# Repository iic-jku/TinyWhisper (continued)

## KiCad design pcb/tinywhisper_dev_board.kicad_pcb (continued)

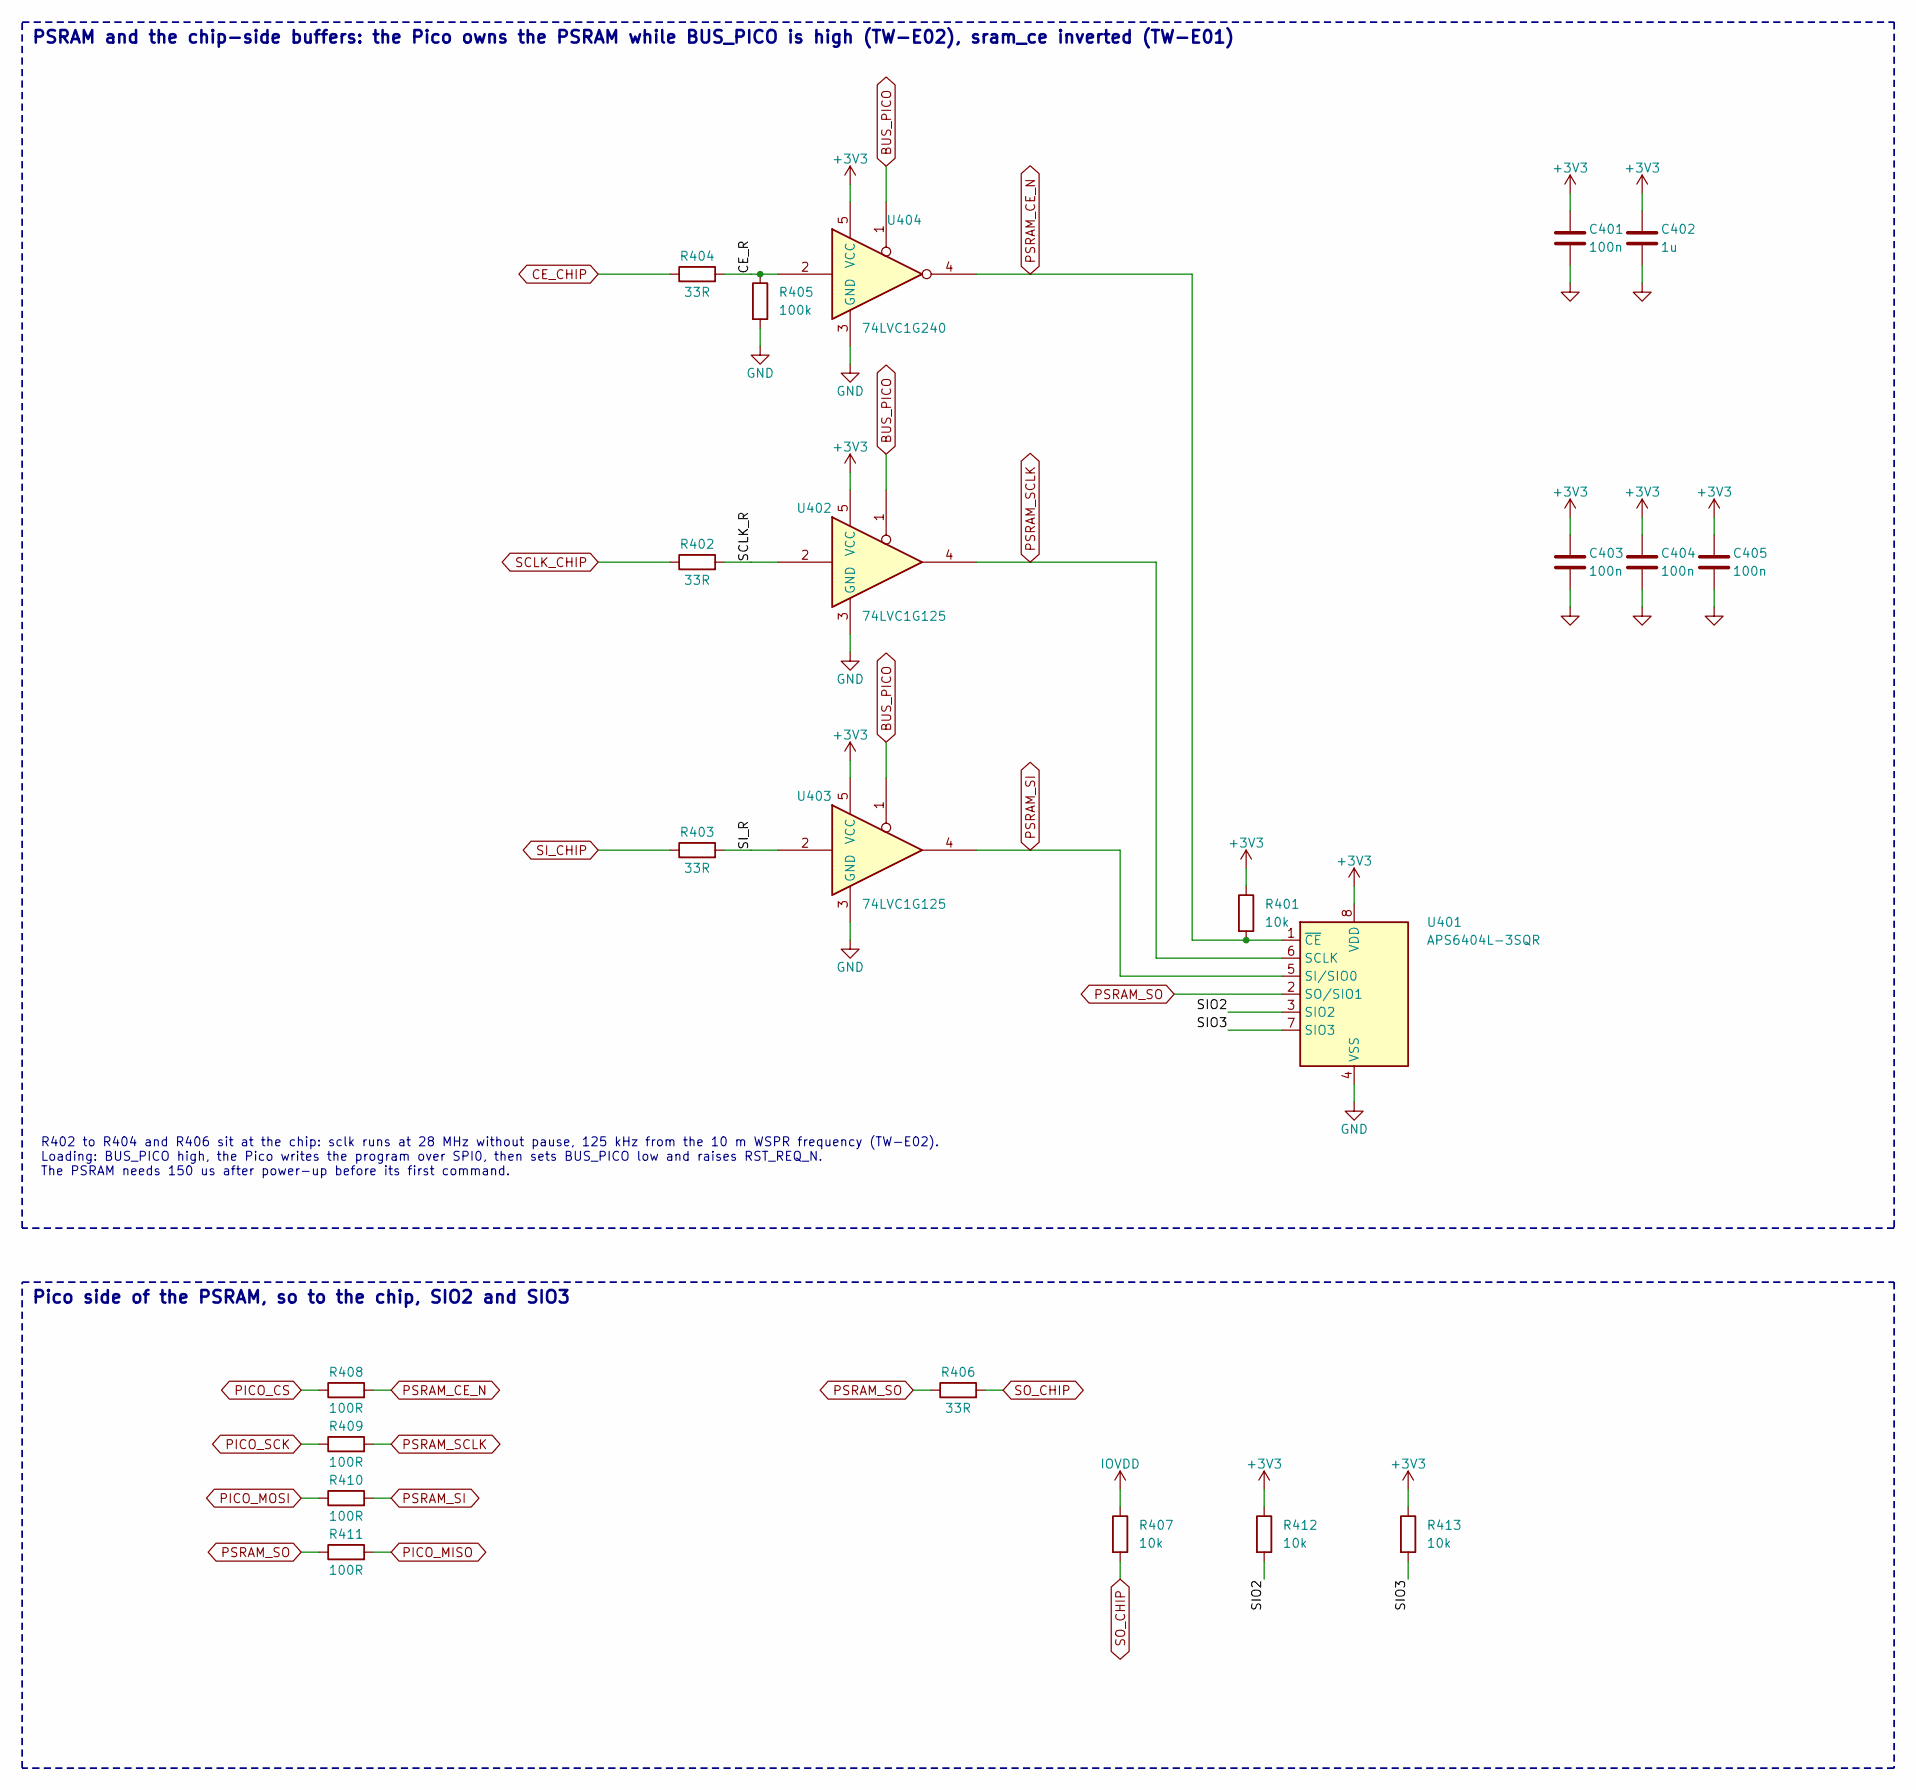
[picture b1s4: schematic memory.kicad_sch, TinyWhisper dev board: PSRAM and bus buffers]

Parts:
C401, C403, C404, C405: 100n; C_0603_1608Metric_Pad1.08x0.95mm_HandSolder; MPN CL10B104KB8NNNC
C402: 1u; C_0603_1608Metric_Pad1.08x0.95mm_HandSolder; MPN CL10B105KO8NNNC
R401, R407, R412, R413: 10k; R_0603_1608Metric_Pad0.98x0.95mm_HandSolder; MPN RC0603FR-0710KL
R402, R403, R404, R406: 33R; R_0603_1608Metric_Pad0.98x0.95mm_HandSolder; MPN RC0603FR-0733RL
R405: 100k; R_0603_1608Metric_Pad0.98x0.95mm_HandSolder; MPN RC0603FR-07100KL
R408, R409, R410, R411: 100R; R_0603_1608Metric_Pad0.98x0.95mm_HandSolder; MPN RC0603FR-07100RL
U401: APS6404L-3SQR; SOIC-8_3.9x4.9mm_P1.27mm; MPN APS6404L-3SQR-SN
U402, U403: 74LVC1G125; SOT-23-5; MPN SN74LVC1G125DBVR
U404: 74LVC1G240; SOT-23-5; MPN SN74LVC1G240DBVR

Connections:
+3V3: C401.1, C402.1, C403.1, C404.1, C405.1, R401.1, R412.1, R413.1, U401.8 (VDD), U402.5 (VCC), U403.5 (VCC), U404.5 (VCC); also elsewhere on the board
/Memory/CE_R: R404.2, R405.1, U404.2
/Memory/SCLK_R: R402.2, U402.2
/Memory/SIO2: R412.2, U401.3 (SIO2)
/Memory/SIO3: R413.2, U401.7 (SIO3)
/Memory/SI_R: R403.2, U403.2
BUS_PICO: U402.1, U403.1, U404.1; also elsewhere on the board
CE_CHIP: R404.1; also elsewhere on the board
GND: C401.2, C402.2, C403.2, C404.2, C405.2, R405.2, U401.4 (VSS), U402.3 (GND), U403.3 (GND), U404.3 (GND); also elsewhere on the board
IOVDD: R407.1; also elsewhere on the board
PICO_CS: R408.1; also elsewhere on the board
PICO_MISO: R411.2; also elsewhere on the board
PICO_MOSI: R410.1; also elsewhere on the board
PICO_SCK: R409.1; also elsewhere on the board
PSRAM_CE_N: R401.2, R408.2, U401.1 (~CE), U404.4
PSRAM_SCLK: R409.2, U401.6 (SCLK), U402.4
PSRAM_SI: R410.2, U401.5 (SI/SIO0), U403.4
PSRAM_SO: R406.1, R411.1, U401.2 (SO/SIO1)
SCLK_CHIP: R402.1; also elsewhere on the board
SI_CHIP: R403.1; also elsewhere on the board
SO_CHIP: R406.2, R407.2; also elsewhere on the board

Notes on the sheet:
PSRAM and the chip-side buffers: the Pico owns the PSRAM while BUS_PICO is high (TW-E02), sram_ce inverted (TW-E01)
R402 to R404 and R406 sit at the chip: sclk runs at 28 MHz without pause, 125 kHz from the 10 m WSPR frequency (TW-E02). Loading: BUS_PICO high, the Pico writes the program over SPI0, then sets BUS_PICO low and raises RST_REQ_N. The PSRAM needs 150 us after power-up before its first command.
Pico side of the PSRAM, so to the chip, SIO2 and SIO3

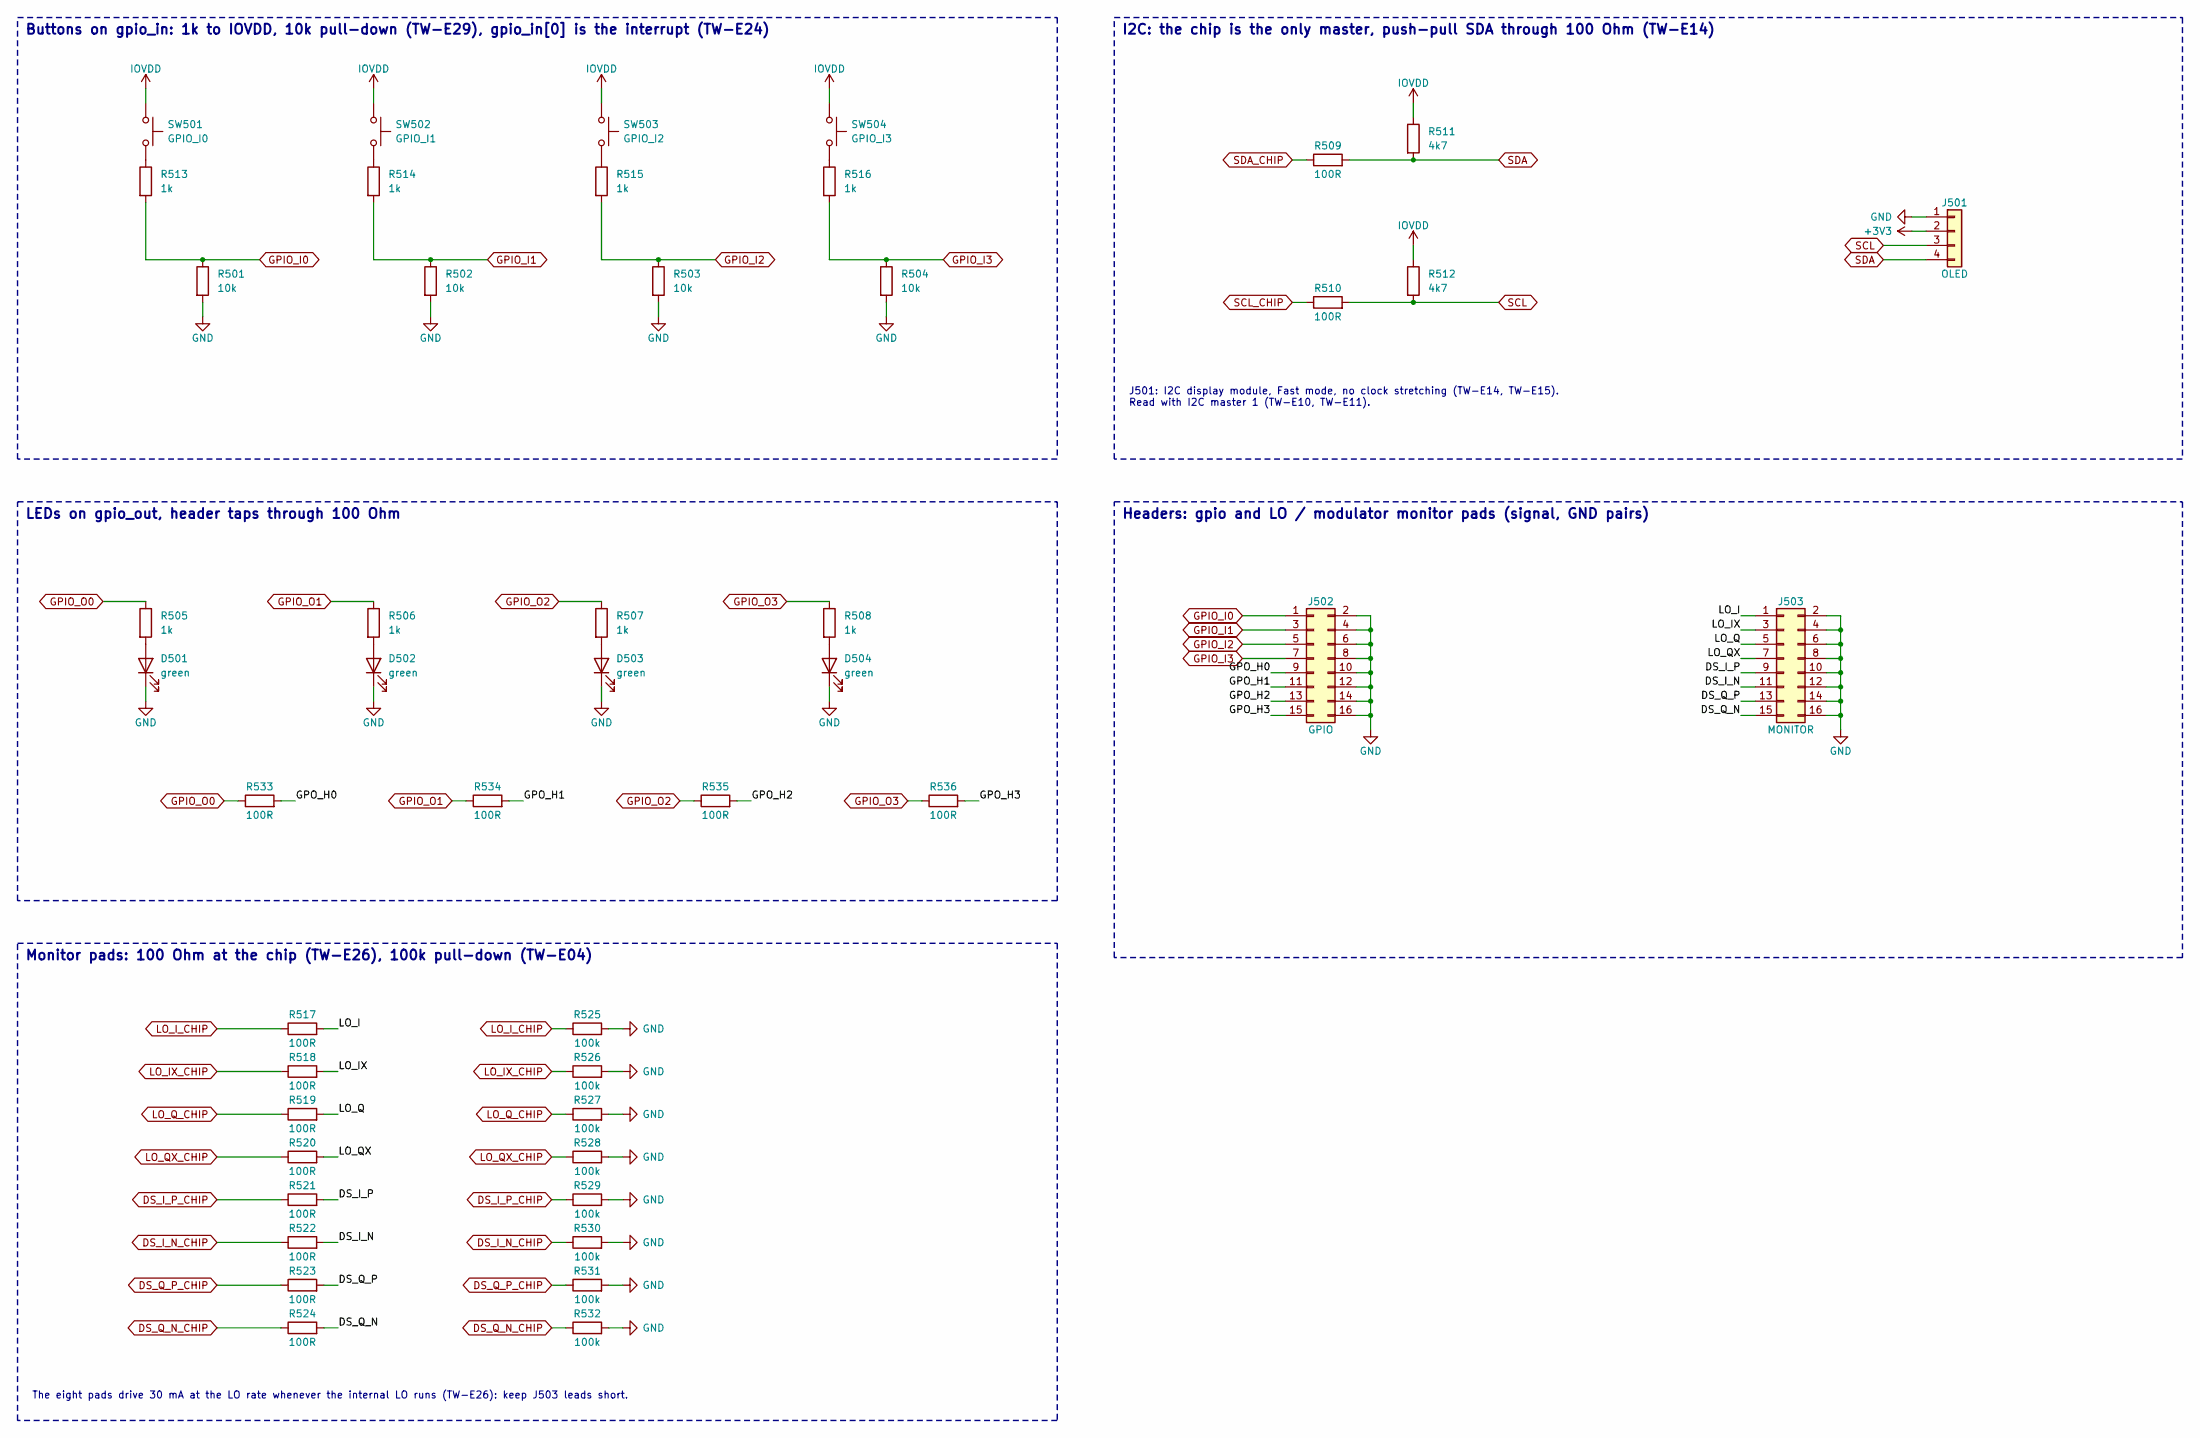
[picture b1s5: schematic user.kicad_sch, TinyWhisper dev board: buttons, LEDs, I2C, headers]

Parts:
D501, D502, D503, D504: green; LED_0603_1608Metric_Pad1.05x0.95mm_HandSolder; MPN APT1608LZGCK
J501: OLED; PinHeader_1x04_P2.54mm_Vertical
J502: GPIO; PinHeader_2x08_P2.54mm_Vertical
J503: MONITOR; PinHeader_2x08_P2.54mm_Vertical
R501, R502, R503, R504: 10k; R_0603_1608Metric_Pad0.98x0.95mm_HandSolder; MPN RC0603FR-0710KL
R505, R506, R507, R508, R513, R514, R515, R516: 1k; R_0603_1608Metric_Pad0.98x0.95mm_HandSolder; MPN RC0603FR-071KL
R509, R510, R517, R518, R519, R520, R521, R522, R523, R524, R533, R534, R535, R536: 100R; R_0603_1608Metric_Pad0.98x0.95mm_HandSolder; MPN RC0603FR-07100RL
R511, R512: 4k7; R_0603_1608Metric_Pad0.98x0.95mm_HandSolder; MPN RC0603FR-074K7L
R525, R526, R527, R528, R529, R530, R531, R532: 100k; R_0603_1608Metric_Pad0.98x0.95mm_HandSolder; MPN RC0603FR-07100KL
SW501: GPIO_I0; SW_TH_Tactile_Omron_B3F-100x; MPN B3F-1000
SW502: GPIO_I1; SW_TH_Tactile_Omron_B3F-100x; MPN B3F-1000
SW503: GPIO_I2; SW_TH_Tactile_Omron_B3F-100x; MPN B3F-1000
SW504: GPIO_I3; SW_TH_Tactile_Omron_B3F-100x; MPN B3F-1000

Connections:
+3V3: J501.2; also elsewhere on the board
/User IO/DS_I_N: J503.11, R522.2
/User IO/DS_I_P: J503.9, R521.2
/User IO/DS_Q_N: J503.15, R524.2
/User IO/DS_Q_P: J503.13, R523.2
/User IO/GPO_H0: J502.9, R533.2
/User IO/GPO_H1: J502.11, R534.2
/User IO/GPO_H2: J502.13, R535.2
/User IO/GPO_H3: J502.15, R536.2
/User IO/LO_I: J503.1, R517.2
/User IO/LO_IX: J503.3, R518.2
/User IO/LO_Q: J503.5, R519.2
/User IO/LO_QX: J503.7, R520.2
DS_I_N_CHIP: R522.1, R530.1; also elsewhere on the board
DS_I_P_CHIP: R521.1, R529.1; also elsewhere on the board
DS_Q_N_CHIP: R524.1, R532.1; also elsewhere on the board
DS_Q_P_CHIP: R523.1, R531.1; also elsewhere on the board
GND: D501.1 (K), D502.1 (K), D503.1 (K), D504.1 (K), J501.1, J502.2, J502.4, J502.6, J502.8, J502.10, J502.12, J502.14, J502.16, J503.2, J503.4, J503.6, J503.8, J503.10, J503.12, J503.14, J503.16, R501.2, R502.2, R503.2, R504.2, R525.2, R526.2, R527.2, R528.2, R529.2, R530.2, R531.2, R532.2; also elsewhere on the board
GPIO_I0: J502.1, R501.1, R513.2; also elsewhere on the board
GPIO_I1: J502.3, R502.1, R514.2; also elsewhere on the board
GPIO_I2: J502.5, R503.1, R515.2; also elsewhere on the board
GPIO_I3: J502.7, R504.1, R516.2; also elsewhere on the board
GPIO_O0: R505.1, R533.1; also elsewhere on the board
GPIO_O1: R506.1, R534.1; also elsewhere on the board
GPIO_O2: R507.1, R535.1; also elsewhere on the board
GPIO_O3: R508.1, R536.1; also elsewhere on the board
IOVDD: R511.1, R512.1, SW501.1, SW502.1, SW503.1, SW504.1; also elsewhere on the board
LO_IX_CHIP: R518.1, R526.1; also elsewhere on the board
LO_I_CHIP: R517.1, R525.1; also elsewhere on the board
LO_QX_CHIP: R520.1, R528.1; also elsewhere on the board
LO_Q_CHIP: R519.1, R527.1; also elsewhere on the board
unnamed: D501.2 (A), R505.2
unnamed: D502.2 (A), R506.2
unnamed: D503.2 (A), R507.2
unnamed: D504.2 (A), R508.2
unnamed: R513.1, SW501.2
unnamed: R514.1, SW502.2
unnamed: R515.1, SW503.2
unnamed: R516.1, SW504.2
SCL: J501.3, R510.2, R512.2; also elsewhere on the board
SCL_CHIP: R510.1; also elsewhere on the board
SDA: J501.4, R509.2, R511.2; also elsewhere on the board
SDA_CHIP: R509.1; also elsewhere on the board

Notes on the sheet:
Buttons on gpio_in: 1k to IOVDD, 10k pull-down (TW-E29), gpio_in[0] is the interrupt (TW-E24)
LEDs on gpio_out, header taps through 100 Ohm
I2C: the chip is the only master, push-pull SDA through 100 Ohm (TW-E14)
J501: I2C display module, Fast mode, no clock stretching (TW-E14, TW-E15). Read with I2C master 1 (TW-E10, TW-E11).
Headers: gpio and LO / modulator monitor pads (signal, GND pairs)
Monitor pads: 100 Ohm at the chip (TW-E26), 100k pull-down (TW-E04)
The eight pads drive 30 mA at the LO rate whenever the internal LO runs (TW-E26): keep J503 leads short.

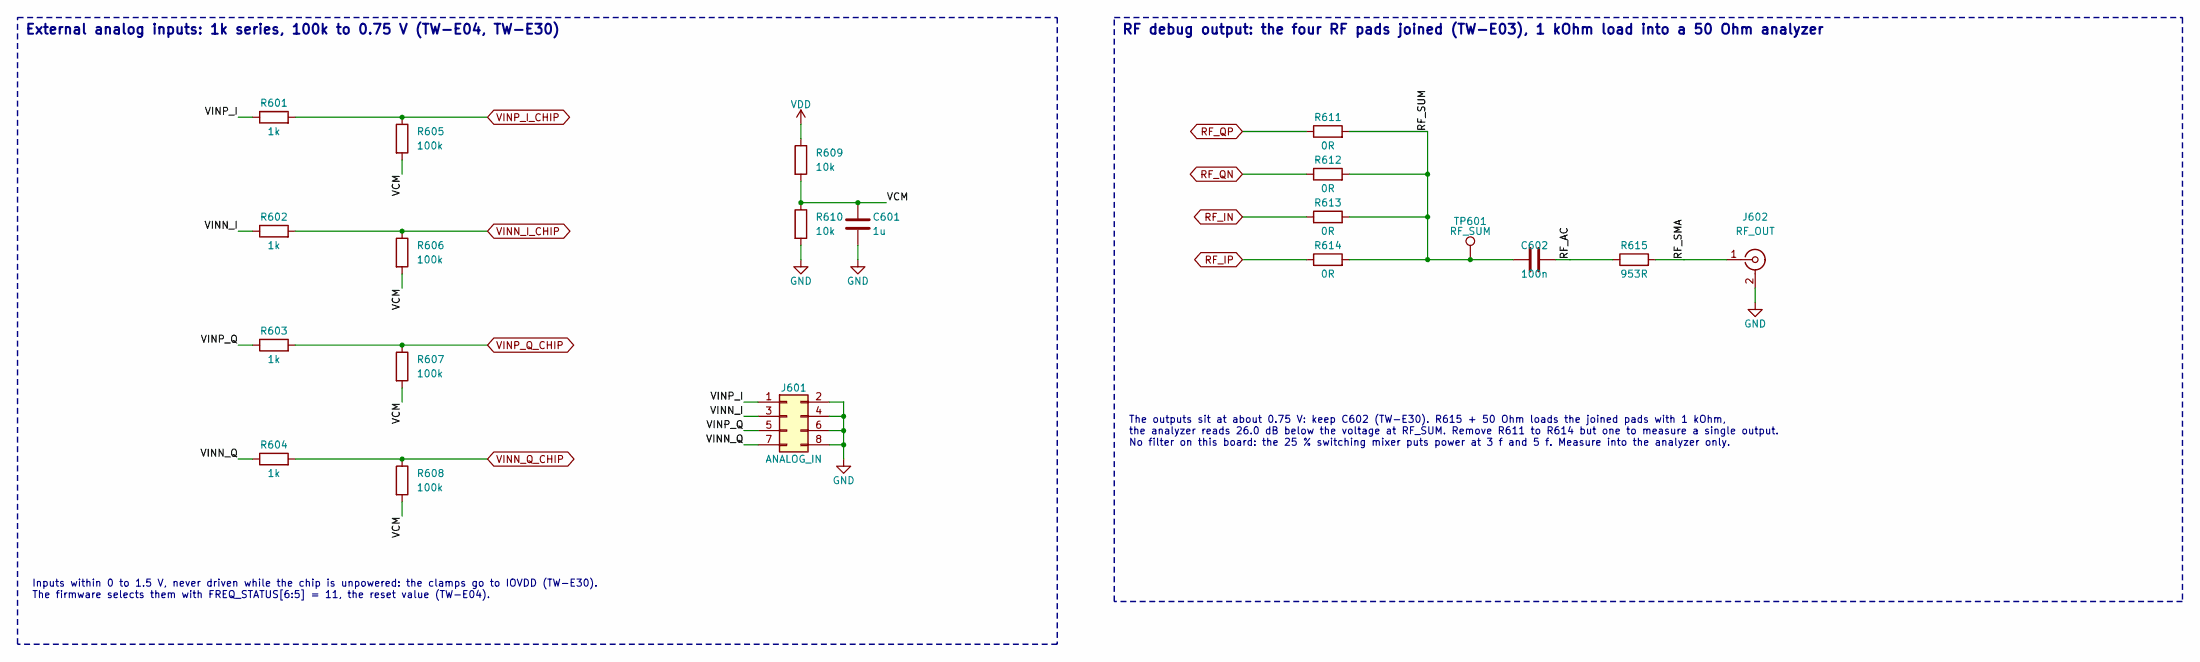
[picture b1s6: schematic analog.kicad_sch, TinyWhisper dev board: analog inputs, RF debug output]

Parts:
C601: 1u; C_0603_1608Metric_Pad1.08x0.95mm_HandSolder; MPN CL10B105KO8NNNC
C602: 100n; C_0603_1608Metric_Pad1.08x0.95mm_HandSolder; MPN CL10B104KB8NNNC
J601: ANALOG_IN; PinHeader_2x04_P2.54mm_Vertical
J602: RF_OUT; SMA_Cinch_142-0761-881_EndLaunch; MPN 142-0761-881
R601, R602, R603, R604: 1k; R_0603_1608Metric_Pad0.98x0.95mm_HandSolder; MPN RC0603FR-071KL
R605, R606, R607, R608: 100k; R_0603_1608Metric_Pad0.98x0.95mm_HandSolder; MPN RC0603FR-07100KL
R609, R610: 10k; R_0603_1608Metric_Pad0.98x0.95mm_HandSolder; MPN RC0603FR-0710KL
R611, R612, R613, R614: 0R; R_0603_1608Metric_Pad0.98x0.95mm_HandSolder; MPN RC0603JR-070RL
R615: 953R; R_0603_1608Metric_Pad0.98x0.95mm_HandSolder; MPN RC0603FR-07953RL
TP601: RF_SUM; TestPoint_Keystone_5000-5004_Miniature; MPN 5000

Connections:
/Analog and RF/RF_AC: C602.2, R615.1
/Analog and RF/RF_SMA: J602.1 (In), R615.2
/Analog and RF/RF_SUM: C602.1, R611.2, R612.2, R613.2, R614.2, TP601.1
/Analog and RF/VCM: C601.1, R605.2, R606.2, R607.2, R608.2, R609.2, R610.1
/Analog and RF/VINN_I: J601.3, R602.1
/Analog and RF/VINN_Q: J601.7, R604.1
/Analog and RF/VINP_I: J601.1, R601.1
/Analog and RF/VINP_Q: J601.5, R603.1
GND: C601.2, J601.2, J601.4, J601.6, J601.8, J602.2 (Ext), R610.2; also elsewhere on the board
RF_IN: R613.1; also elsewhere on the board
RF_IP: R614.1; also elsewhere on the board
RF_QN: R612.1; also elsewhere on the board
RF_QP: R611.1; also elsewhere on the board
VDD: R609.1; also elsewhere on the board
VINN_I_CHIP: R602.2, R606.1; also elsewhere on the board
VINN_Q_CHIP: R604.2, R608.1; also elsewhere on the board
VINP_I_CHIP: R601.2, R605.1; also elsewhere on the board
VINP_Q_CHIP: R603.2, R607.1; also elsewhere on the board

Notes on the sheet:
External analog inputs: 1k series, 100k to 0.75 V (TW-E04, TW-E30)
Inputs within 0 to 1.5 V, never driven while the chip is unpowered: the clamps go to IOVDD (TW-E30). The firmware selects them with FREQ_STATUS[6:5] = 11, the reset value (TW-E04).
RF debug output: the four RF pads joined (TW-E03), 1 kOhm load into a 50 Ohm analyzer
The outputs sit at about 0.75 V: keep C602 (TW-E30). R615 + 50 Ohm loads the joined pads with 1 kOhm, the analyzer reads 26.0 dB below the voltage at RF_SUM. Remove R611 to R614 but one to measure a single output. No filter on this board: the 25 % switching mixer puts power at 3 f and 5 f. Measure 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

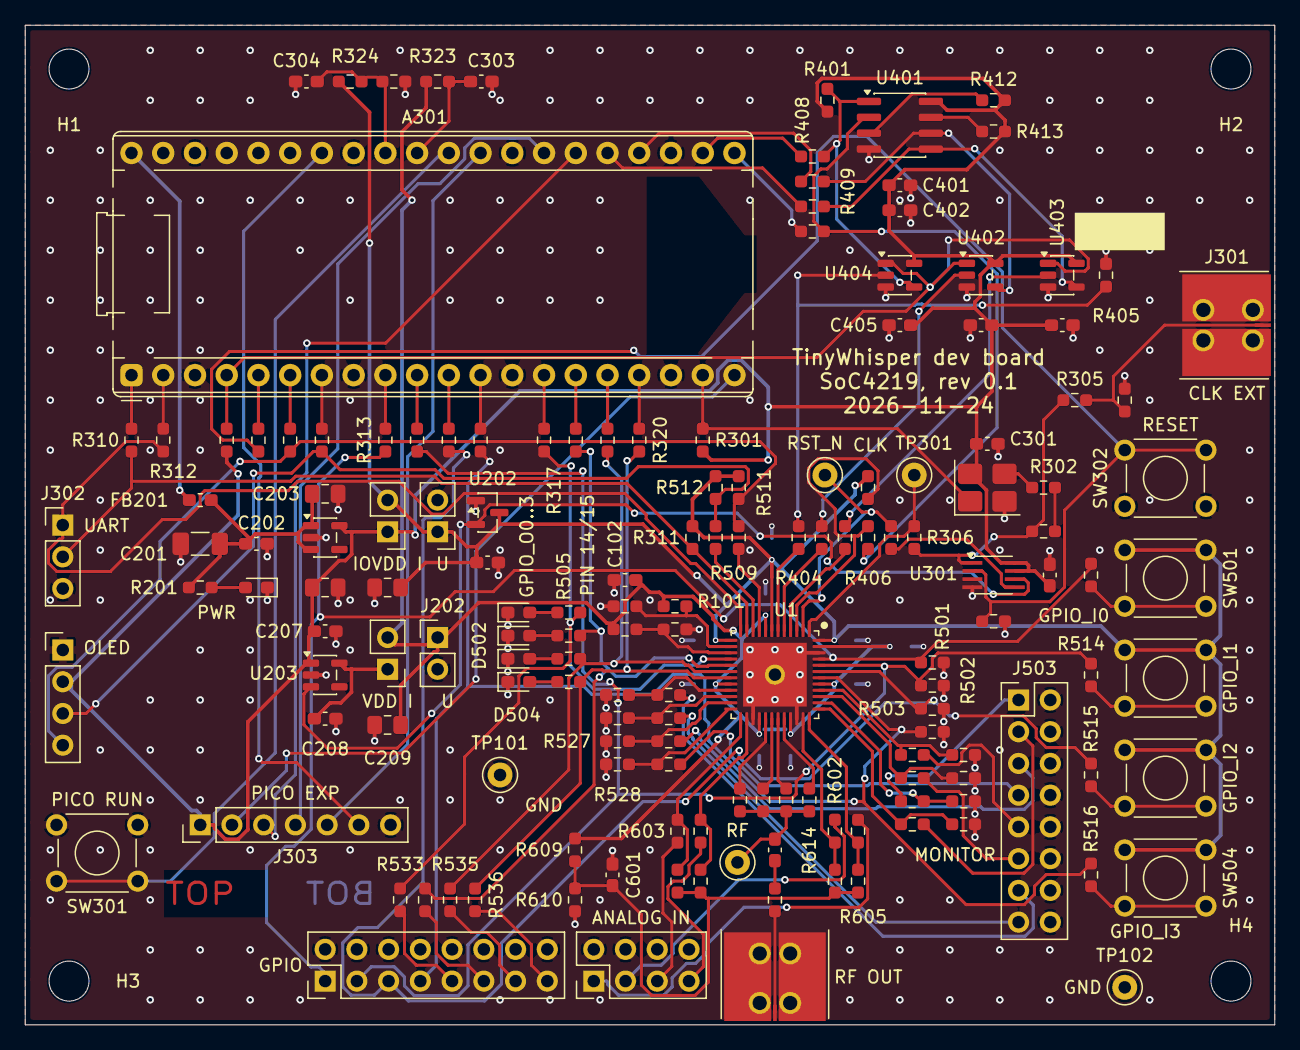
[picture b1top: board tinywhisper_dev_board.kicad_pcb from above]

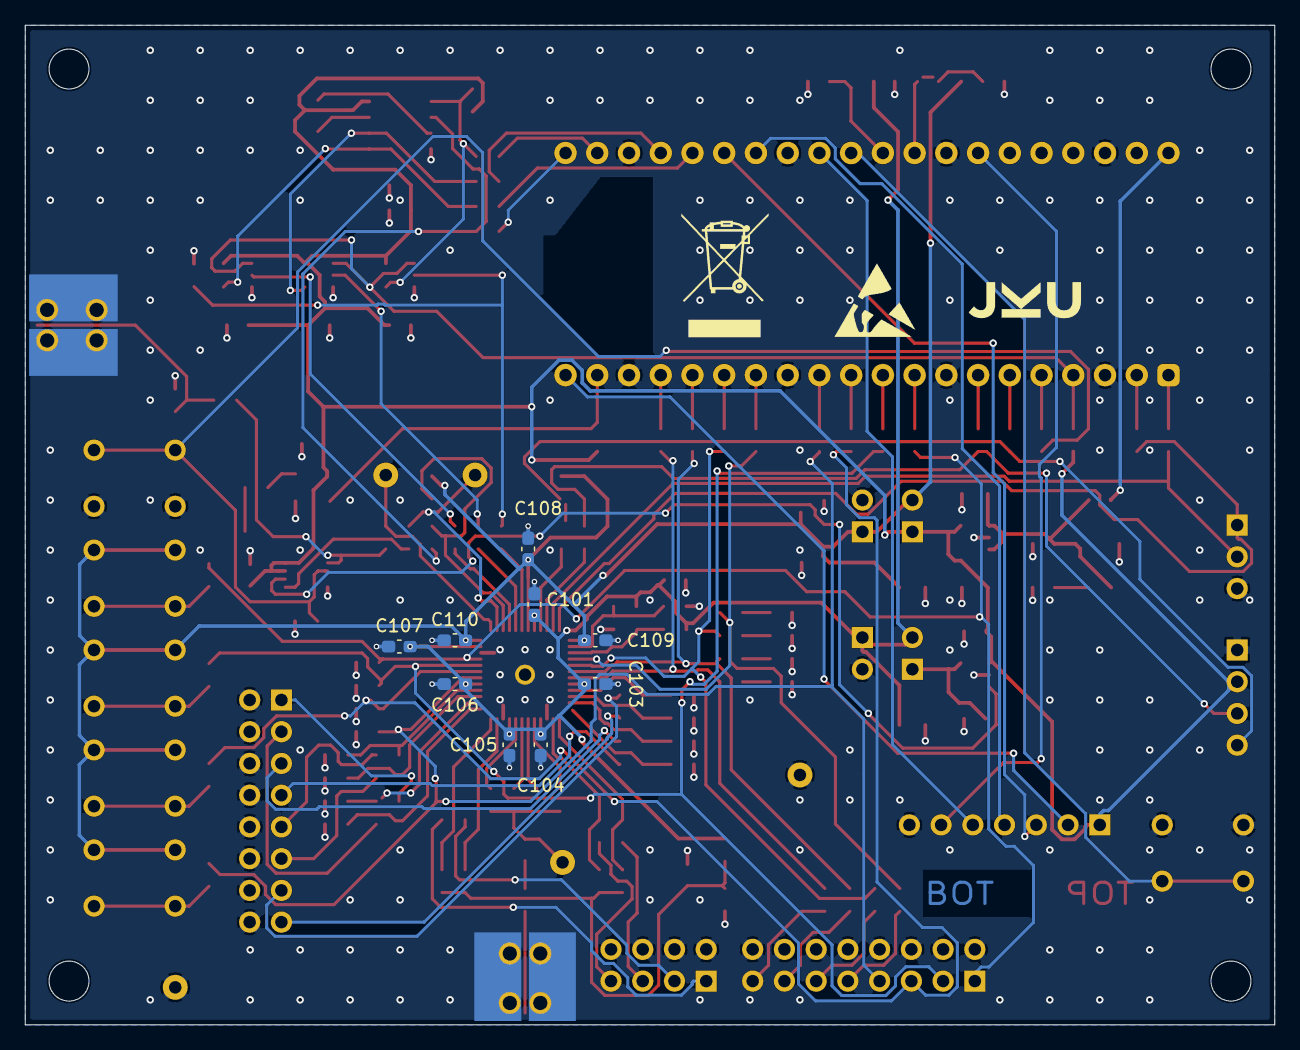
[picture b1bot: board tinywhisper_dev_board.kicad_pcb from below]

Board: 4 copper layers, 100.0 x 80.0 mm, 172 parts (12 on the bottom side), 117 nets.

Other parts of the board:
LOGO1: Logo_JKU_9.0x2.9mm
LOGO2: Logo_ESD_6.5x5.9mm
LOGO3: Logo_WEEE_7.0x9.9mm
